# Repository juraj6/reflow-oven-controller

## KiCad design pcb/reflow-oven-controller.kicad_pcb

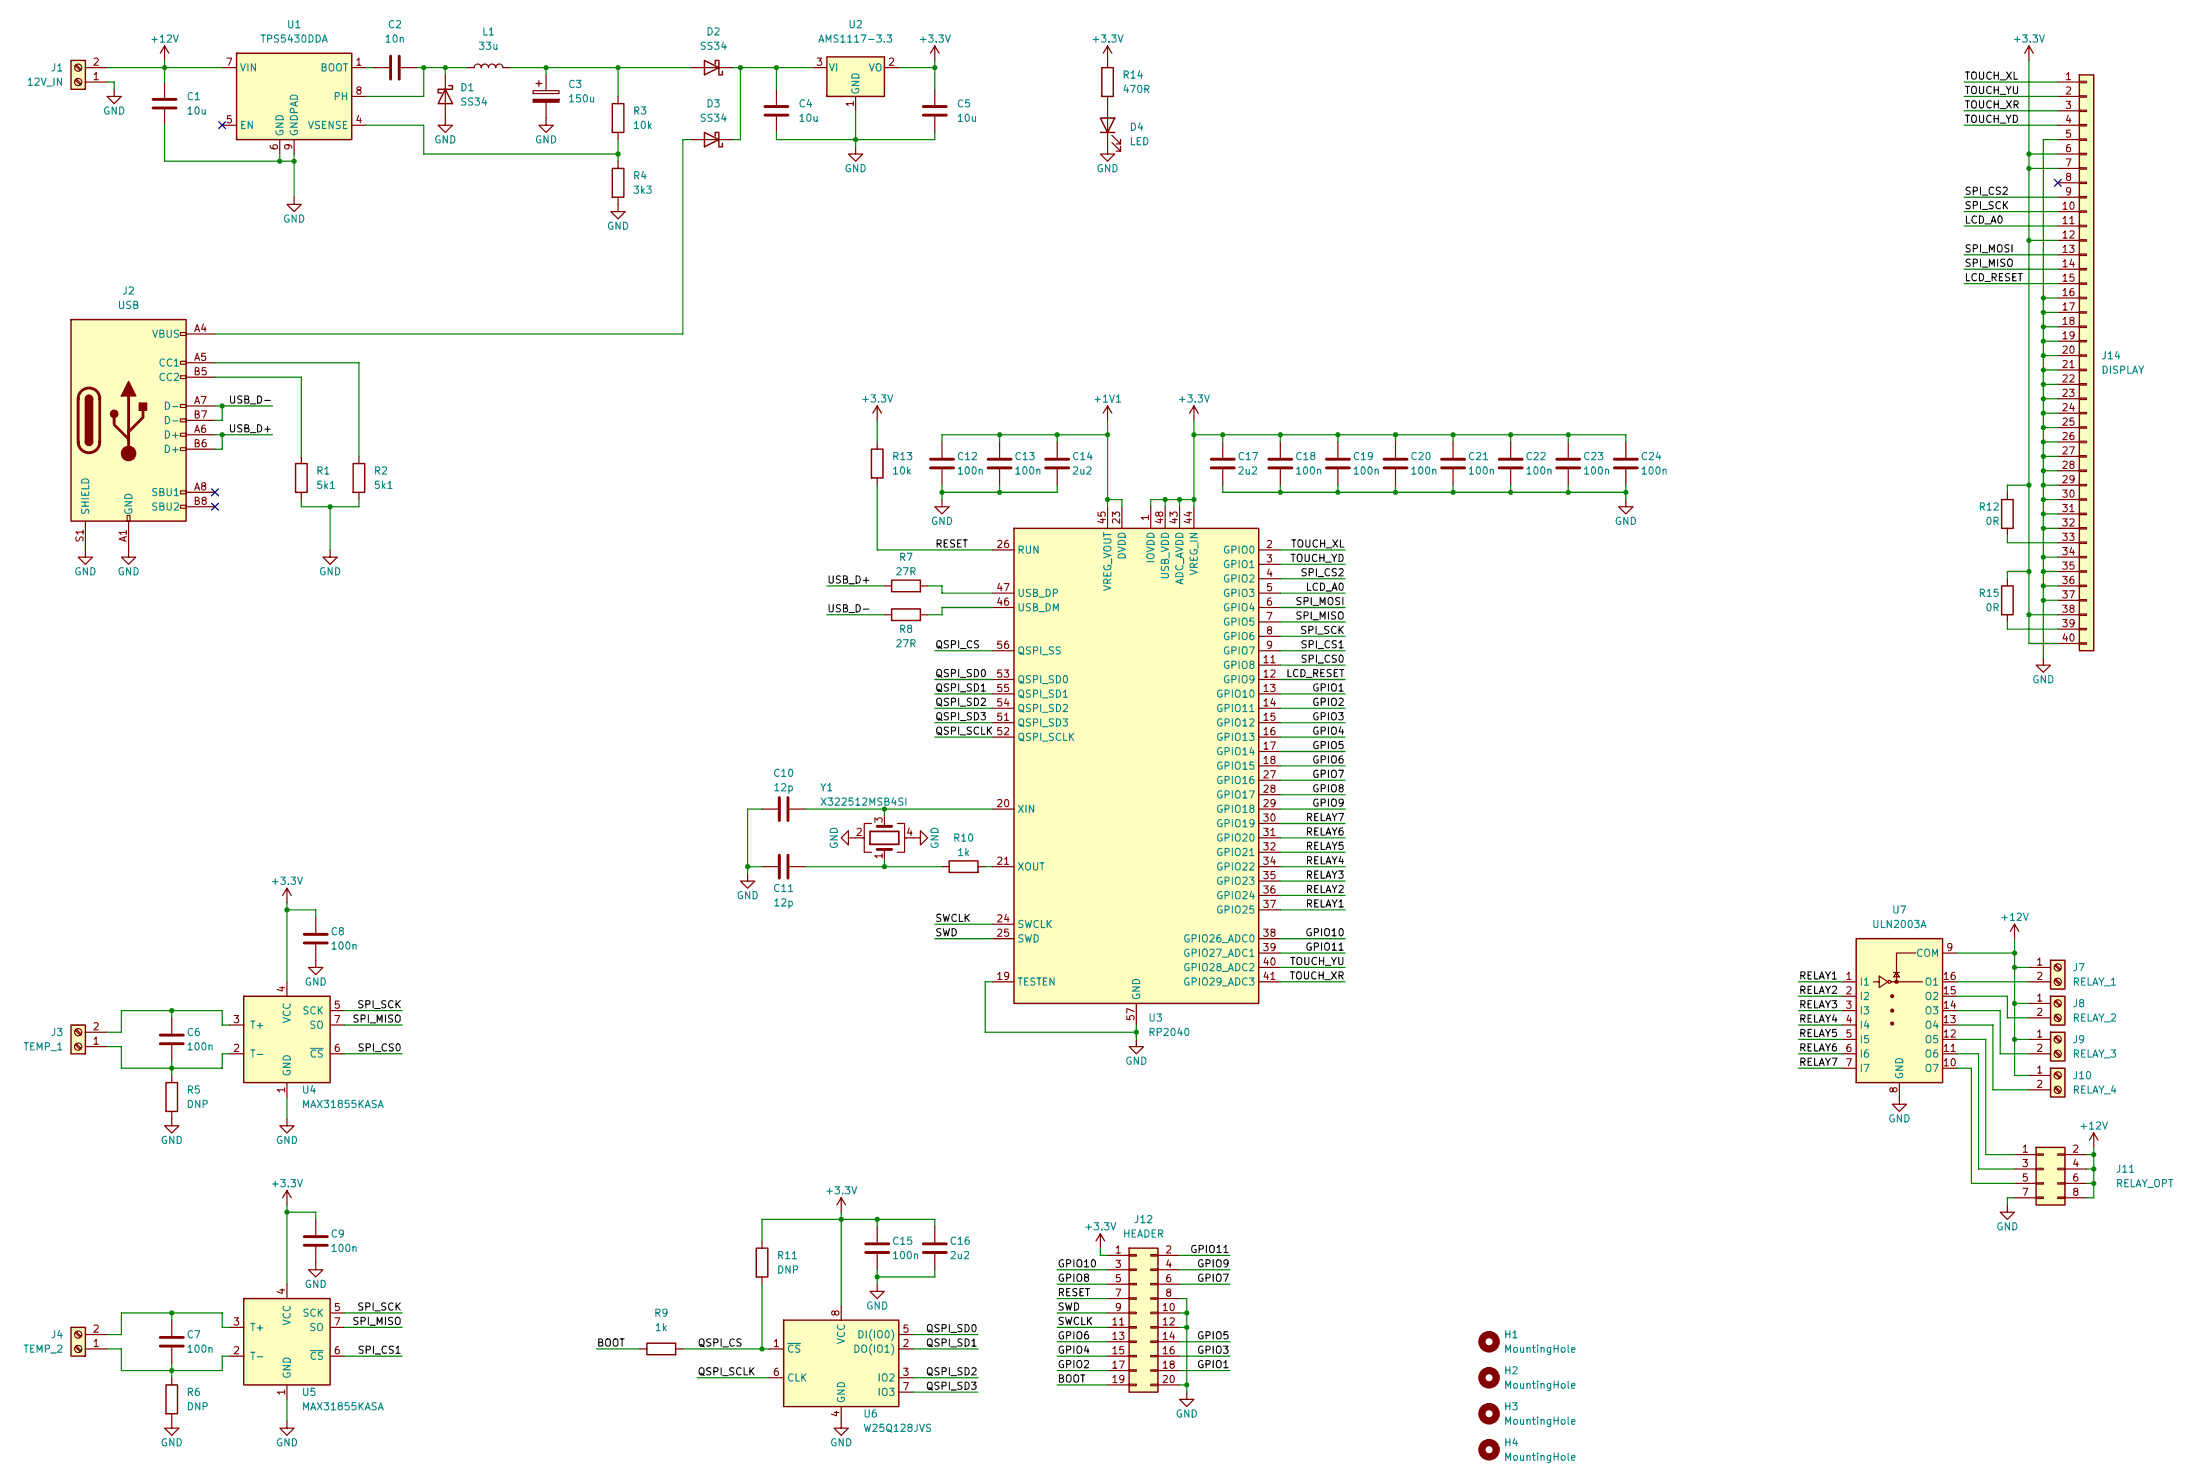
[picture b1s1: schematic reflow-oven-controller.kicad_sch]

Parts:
C1, C4, C5: 10u; C_0805_2012Metric; Tolerance 10%; Voltage 25V; LCSC C15850
C2: 10n; C_0402_1005Metric; Tolerance 10%; Voltage 50V; LCSC C15195
C3: 150u; CP_EIA-7343-15_Kemet-W; Tolerance 20%; Voltage 10V; LCSC C347559
C6, C7, C8, C9, C12, C13, C15, C18, C19, C20, C21, C22, C23, C24: 100n; C_0402_1005Metric; Tolerance 10%; Voltage 16V; LCSC C1525
C10, C11: 12p; C_0402_1005Metric; Tolerance 5%; Voltage 50V; LCSC C1547
C14, C16, C17: 2u2; C_0402_1005Metric; Tolerance 20%; Voltage 6.3V; LCSC C12530
D1, D2, D3: SS34; D_SMA; Voltage 40V; LCSC C8678
D4: LED; LED_0603_1608Metric; LCSC C72043
H1, H2, H3, H4: MountingHole; MountingHole_3.2mm_M3
J1: 12V_IN; TerminalBlock_MetzConnect_Type059_RT06302HBWC_1x02_P3.50mm_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
J2: USB; GCT_USB4145-03-0070-C_REVA2
J3: TEMP_1; TerminalBlock_MetzConnect_Type059_RT06302HBWC_1x02_P3.50mm_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
J4: TEMP_2; TerminalBlock_MetzConnect_Type059_RT06302HBWC_1x02_P3.50mm_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
J7: RELAY_1; TerminalBlock_MetzConnect_Type059_RT06302HBWC_1x02_P3.50mm_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
J8: RELAY_2; TerminalBlock_MetzConnect_Type059_RT06302HBWC_1x02_P3.50mm_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
J9: RELAY_3; TerminalBlock_MetzConnect_Type059_RT06302HBWC_1x02_P3.50mm_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
J10: RELAY_4; TerminalBlock_MetzConnect_Type059_RT06302HBWC_1x02_P3.50mm_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
J11: RELAY_OPT; PinHeader_2x04_P2.54mm_Vertical_SMD
J12: HEADER; PinHeader_2x10_P2.54mm_Vertical_SMD
J14: DISPLAY; Hirose_FH12-40S-0.5SH_1x40-1MP_P0.50mm_Horizontal; LCSC C202114
L1: 33u; L_Taiyo-Yuden_NR-50xx; Tolerance 20%; LCSC C86618
R1, R2: 5k1; R_0402_1005Metric; Tolerance 1%; LCSC C25905
R3, R13: 10k; R_0402_1005Metric; Tolerance 1%; LCSC C25744
R4: 3k3; R_0402_1005Metric; Tolerance 1%; LCSC C25890
R5, R6, R11: DNP; R_0603_1608Metric
R7, R8: 27R; R_0603_1608Metric; Tolerance 1%; LCSC C25190
R9, R10: 1k; R_0402_1005Metric; Tolerance 1%; LCSC C11702
R12, R15: 0R; R_0603_1608Metric; LCSC C21189
R14: 470R; R_0402_1005Metric; Tolerance 1%; LCSC C25117
U1: TPS5430DDA; TI_SO-PowerPAD-8_ThermalVias; LCSC C9864
U2: AMS1117-3.3; SOT-223-3_TabPin2; LCSC C6186
U3: RP2040; QFN-56-1EP_7x7mm_P0.4mm_EP3.2x3.2mm; LCSC C2040
U4, U5: MAX31855KASA; SOIC-8_3.9x4.9mm_P1.27mm; LCSC C52028
U6: W25Q128JVS; SOIC-8_5.23x5.23mm_P1.27mm; LCSC C97521
U7: ULN2003A; SOIC-16_3.9x9.9mm_P1.27mm; LCSC C7512
Y1: X322512MSB4SI; Crystal_SMD_SeikoEpson_TSX3225-4Pin_3.2x2.5mm; LCSC C9002

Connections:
+1V1: C12.1, C13.1, C14.1, U3.23 (DVDD), U3.45 (VREG_VOUT), U3.50 (DVDD)
+3.3V: C5.1, C8.1, C9.1, C15.1, C16.1, C17.1, C18.1, C19.1, C20.1, C21.1, C22.1, C23.1, C24.1, J12.1, J14.6, J14.7, J14.12, J14.38, J14.40, R11.1, R12.1, R13.1, R14.1, R15.1, U2.2 (VO), U3.1 (IOVDD), U3.10 (IOVDD), U3.22 (IOVDD), U3.33 (IOVDD), U3.42 (IOVDD), U3.43 (ADC_AVDD), U3.44 (VREG_IN), U3.48 (USB_VDD), U3.49 (IOVDD), U4.4 (VCC), U5.4 (VCC), U6.8 (VCC)
+12V: C1.1, J1.2, J7.1, J8.1, J9.1, J10.1, J11.2, J11.4, J11.6, J11.8, U1.7 (VIN), U7.9 (COM)
/BOOT: J12.19, R9.1
/GPIO1: J12.18, U3.13 (GPIO10)
/GPIO2: J12.17, U3.14 (GPIO11)
/GPIO3: J12.16, U3.15 (GPIO12)
/GPIO4: J12.15, U3.16 (GPIO13)
/GPIO5: J12.14, U3.17 (GPIO14)
/GPIO6: J12.13, U3.18 (GPIO15)
/GPIO7: J12.6, U3.27 (GPIO16)
/GPIO8: J12.5, U3.28 (GPIO17)
/GPIO9: J12.4, U3.29 (GPIO18)
/GPIO10: J12.3, U3.38 (GPIO26_ADC0)
/GPIO11: J12.2, U3.39 (GPIO27_ADC1)
/LCD_A0: J14.11, U3.5 (GPIO3)
/LCD_RESET: J14.15, U3.12 (GPIO9)
/QSPI_CS: R9.2, R11.2, U3.56 (QSPI_SS), U6.1 (~CS)
/QSPI_SCLK: U3.52 (QSPI_SCLK), U6.6 (CLK)
/QSPI_SD0: U3.53 (QSPI_SD0), U6.5 (DI(IO0))
/QSPI_SD1: U3.55 (QSPI_SD1), U6.2 (DO(IO1))
/QSPI_SD2: U3.54 (QSPI_SD2), U6.3 (IO2)
/QSPI_SD3: U3.51 (QSPI_SD3), U6.7 (IO3)
/RELAY1: U3.37 (GPIO25), U7.1 (I1)
/RELAY2: U3.36 (GPIO24), U7.2 (I2)
/RELAY3: U3.35 (GPIO23), U7.3 (I3)
/RELAY4: U3.34 (GPIO22), U7.4 (I4)
/RELAY5: U3.32 (GPIO21), U7.5 (I5)
/RELAY6: U3.31 (GPIO20), U7.6 (I6)
/RELAY7: U3.30 (GPIO19), U7.7 (I7)
/RESET: J12.7, R13.2, U3.26 (RUN)
/SPI_CS0: U3.11 (GPIO8), U4.6 (~CS)
/SPI_CS1: U3.9 (GPIO7), U5.6 (~CS)
/SPI_CS2: J14.9, U3.4 (GPIO2)
/SPI_MISO: J14.14, U3.7 (GPIO5), U4.7 (SO), U5.7 (SO)
/SPI_MOSI: J14.13, U3.6 (GPIO4)
/SPI_SCK: J14.10, U3.8 (GPIO6), U4.5 (SCK), U5.5 (SCK)
/SWCLK: J12.11, U3.24 (SWCLK)
/SWD: J12.9, U3.25 (SWD)
/TOUCH_XL: J14.1, U3.2 (GPIO0)
/TOUCH_XR: J14.3, U3.41 (GPIO29_ADC3)
/TOUCH_YD: J14.4, U3.3 (GPIO1)
/TOUCH_YU: J14.2, U3.40 (GPIO28_ADC2)
/USB_D+: J2.A6 (D+), J2.B6 (D+), R7.1
/USB_D-: J2.A7 (D-), J2.B7 (D-), R8.1
GND: C1.2, C3.2, C4.2, C5.2, C8.2, C9.2, C10.1, C11.1, C12.2, C13.2, C14.2, C15.2, C16.2, C17.2, C18.2, C19.2, C20.2, C21.2, C22.2, C23.2, C24.2, D1.2 (A), D4.1 (K), J1.1, J2.A1 (GND), J2.A12 (GND), J2.B1 (GND), J2.B12 (GND), J2.S1 (SHIELD), J11.7, J12.8, J12.10, J12.12, J12.20, J14.5, J14.16, J14.17, J14.18, J14.19, J14.20, J14.21, J14.22, J14.23, J14.24, J14.25, J14.26, J14.27, J14.28, J14.29, J14.30, J14.31, J14.32, J14.34, J14.35, J14.36, J14.37, R1.2, R2.2, R4.2, R5.2, R6.2, U1.6 (GND), U1.9 (GNDPAD), U2.1 (GND), U3.19 (TESTEN), U3.57 (GND), U4.1 (GND), U5.1 (GND), U6.4 (GND), U7.8 (GND), Y1.2, Y1.4
unnamed: C2.1, U1.1 (BOOT)
unnamed: C2.2, D1.1 (K), L1.1, U1.8 (PH)
unnamed: C3.1, D2.2 (A), L1.2, R3.1
unnamed: C4.1, D2.1 (K), D3.1 (K), U2.3 (VI)
unnamed: C6.1, J3.2, U4.3 (T+)
unnamed: C6.2, J3.1, R5.1, U4.2 (T-)
unnamed: C7.1, J4.2, U5.3 (T+)
unnamed: C7.2, J4.1, R6.1, U5.2 (T-)
unnamed: C10.2, U3.20 (XIN), Y1.3
unnamed: C11.2, R10.1, Y1.1
unnamed: D3.2 (A), J2.A4 (VBUS), J2.A9 (VBUS), J2.B4 (VBUS), J2.B9 (VBUS)
unnamed: D4.2 (A), R14.2
unnamed: J2.A5 (CC1), R2.1
unnamed: J2.B5 (CC2), R1.1
unnamed: J7.2, U7.16 (O1)
unnamed: J8.2, U7.15 (O2)
unnamed: J9.2, U7.14 (O3)
unnamed: J10.2, U7.13 (O4)
unnamed: J11.1, U7.12 (O5)
unnamed: J11.3, U7.11 (O6)
unnamed: J11.5, U7.10 (O7)
unnamed: J14.33, R12.2
unnamed: J14.39, R15.2
unnamed: R3.2, R4.1, U1.4 (VSENSE)
unnamed: R7.2, U3.47 (USB_DP)
unnamed: R8.2, U3.46 (USB_DM)
unnamed: R10.2, U3.21 (XOUT)

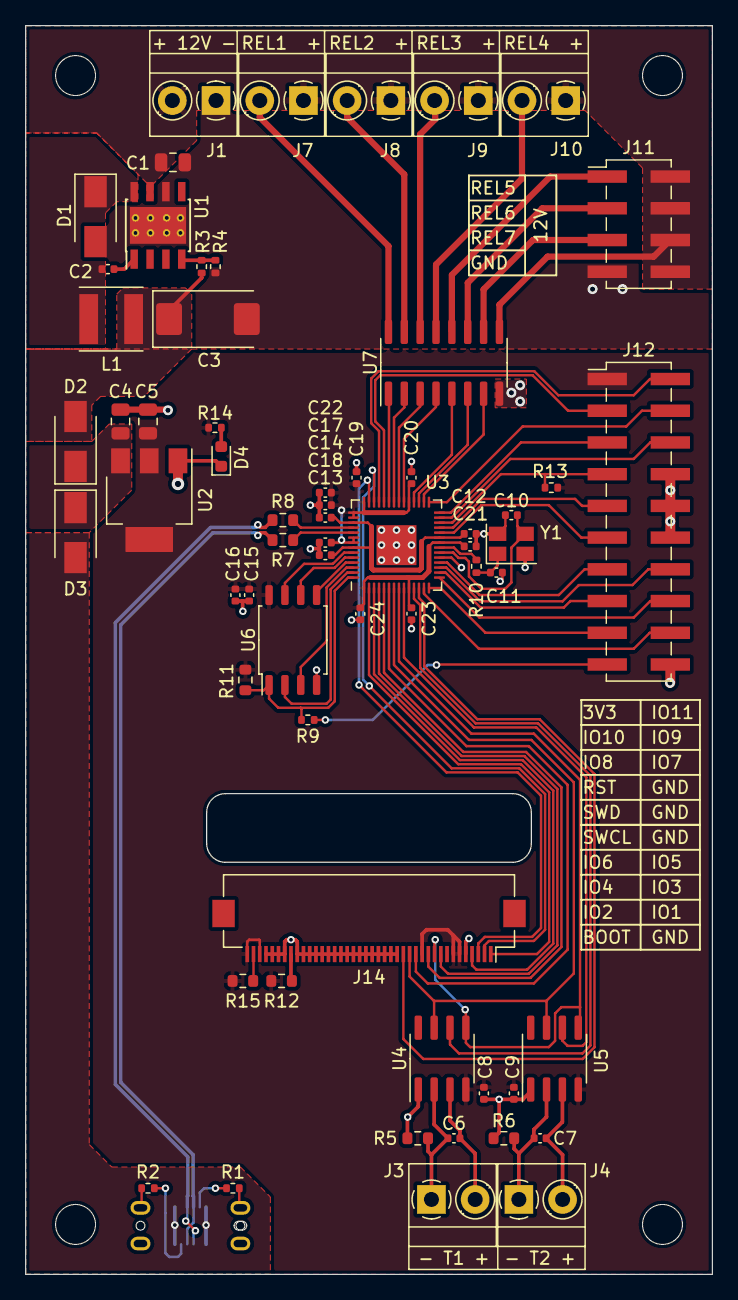
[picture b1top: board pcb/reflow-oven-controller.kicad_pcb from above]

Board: 2 copper layers, 55.0 x 100.0 mm, 67 parts (1 on the bottom side), 73 nets.

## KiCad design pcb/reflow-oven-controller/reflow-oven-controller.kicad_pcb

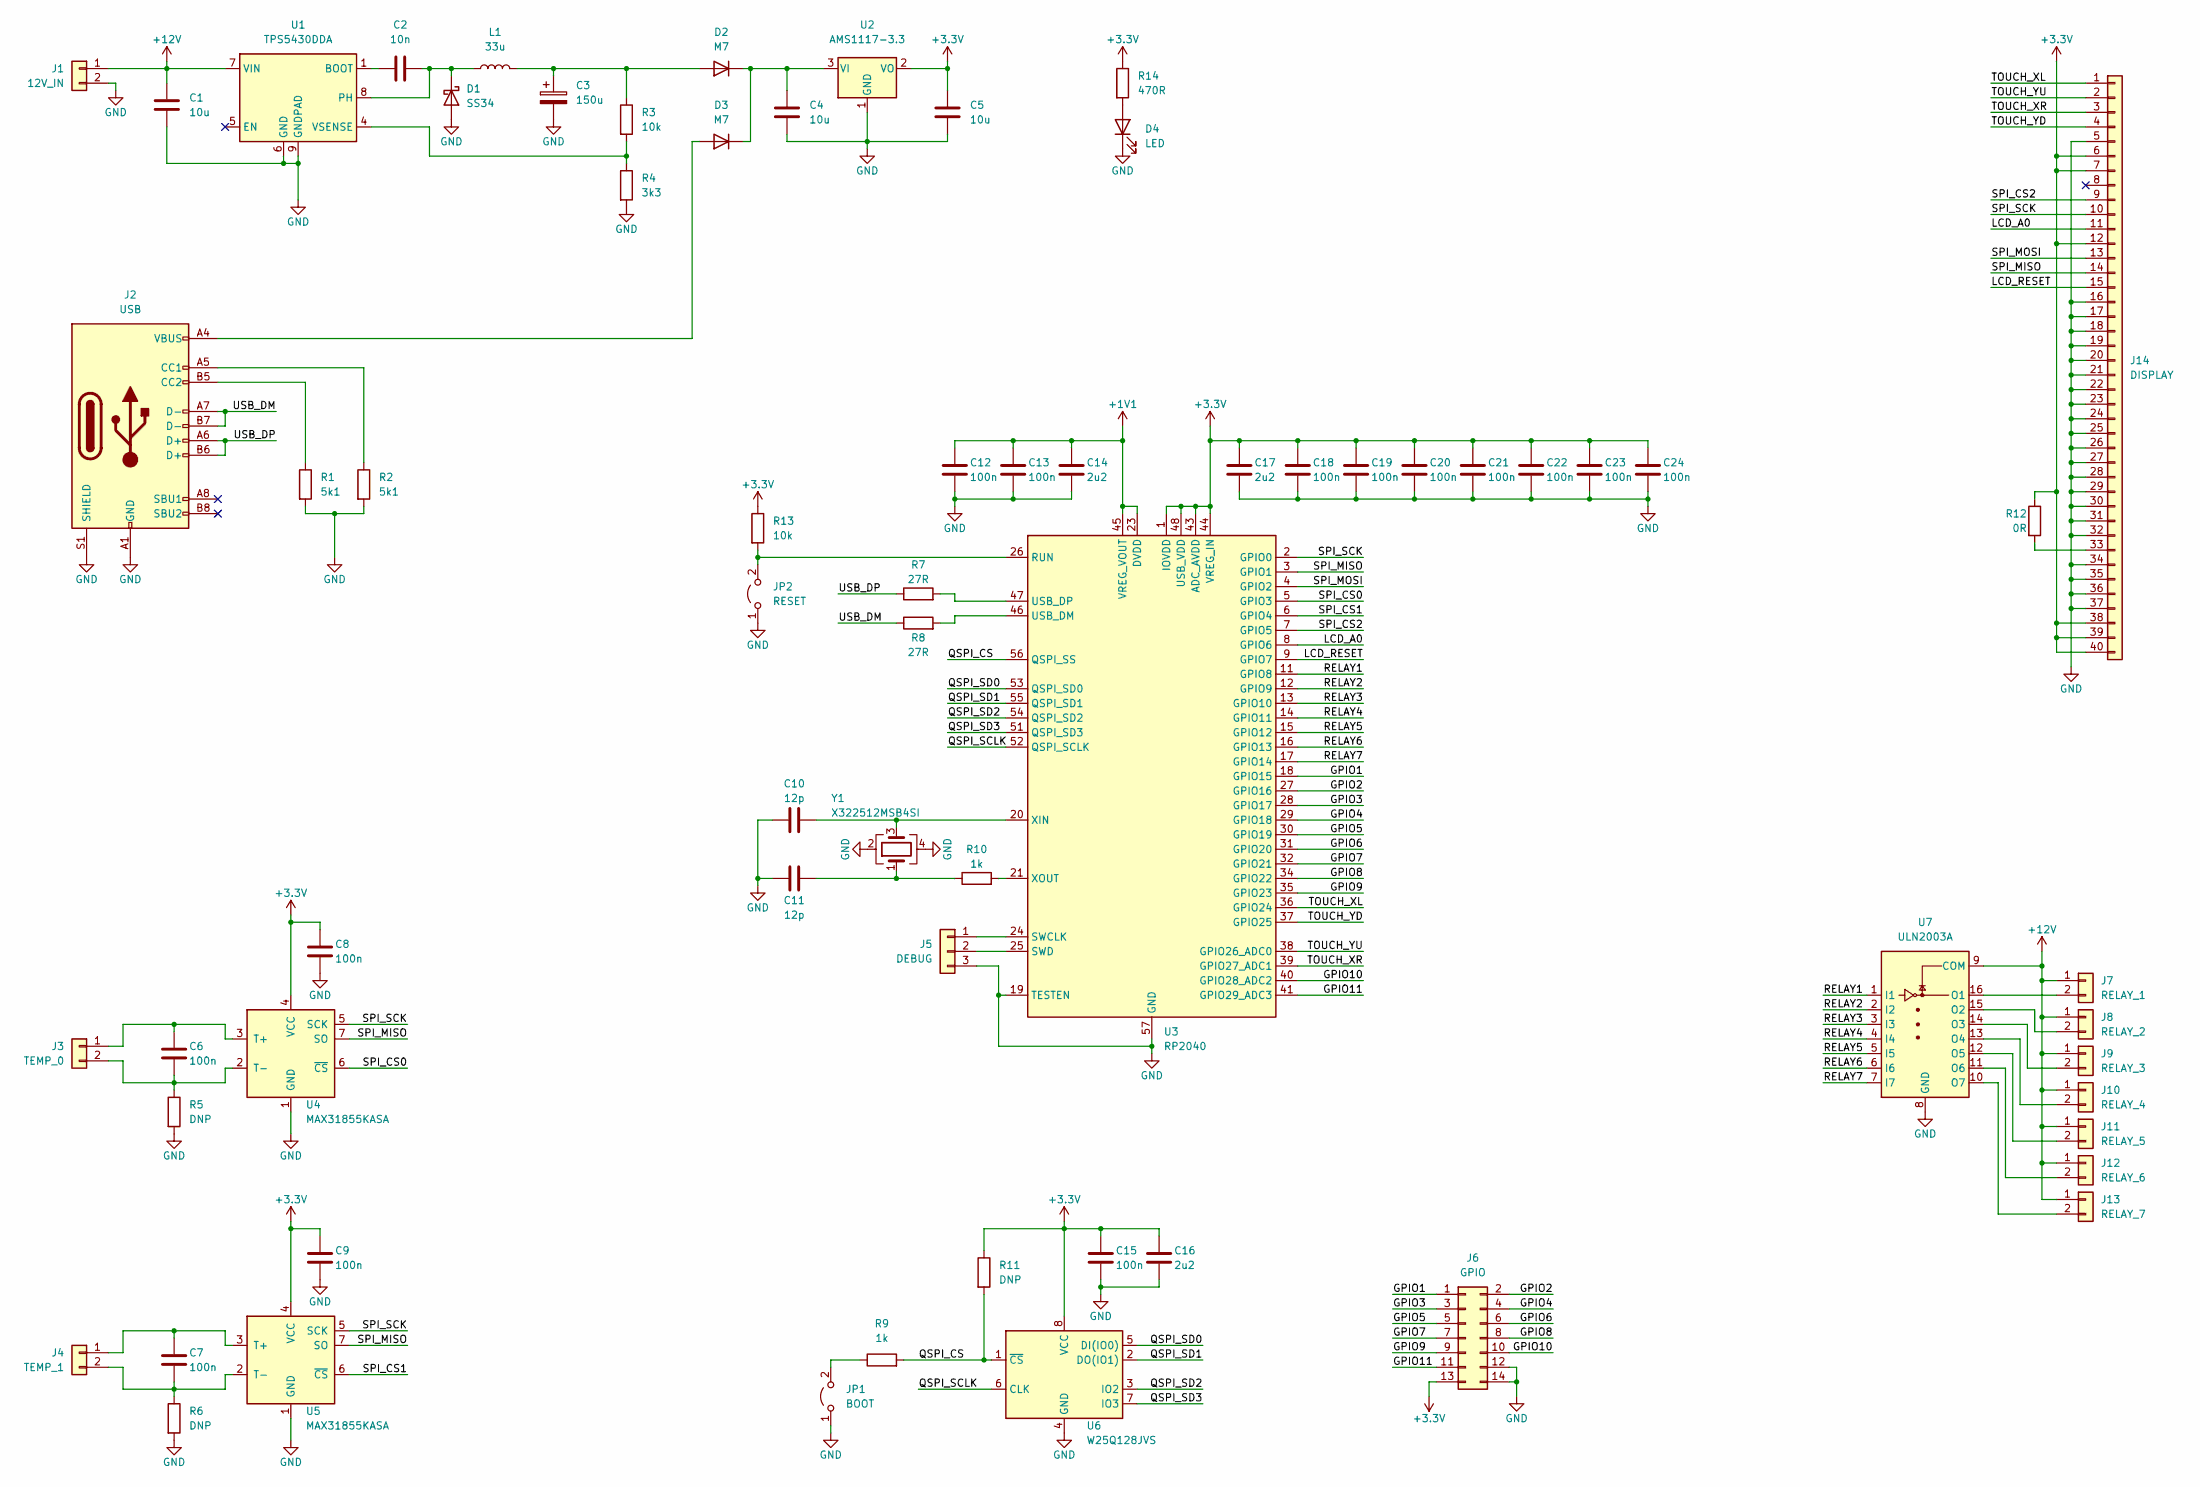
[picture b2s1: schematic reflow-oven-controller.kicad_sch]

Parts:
C1, C4, C5: 10u; C_0805_2012Metric; Tolerance 10%; Voltage 25V; LCSC C15850
C2: 10n; C_0402_1005Metric; Tolerance 10%; Voltage 50V; LCSC C15195
C3: 150u; CP_EIA-7343-15_Kemet-W; Tolerance 20%; Voltage 10V; LCSC C347559
C6, C7, C8, C9, C12, C13, C15, C18, C19, C20, C21, C22, C23, C24: 100n; C_0402_1005Metric; Tolerance 10%; Voltage 16V; LCSC C1525
C10, C11: 12p; C_0402_1005Metric; Tolerance 5%; Voltage 50V; LCSC C1547
C14, C16, C17: 2u2; C_0402_1005Metric; Tolerance 20%; Voltage 6.3V; LCSC C12530
D1: SS34; D_SMA; Voltage 40V; LCSC C8678
D2, D3: M7; D_SMA; LCSC C95872
D4: LED; LED_0603_1608Metric; LCSC C72043
J1: 12V_IN; TerminalBlock_MetzConnect_Type059_RT06302HBWC_1x02_P3.50mm_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
J2: USB; USB_C_Receptacle_GCT_USB4115-03-C; LCSC C381139
J3: TEMP_0; TerminalBlock_MetzConnect_Type059_RT06302HBWC_1x02_P3.50mm_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
J4: TEMP_1; TerminalBlock_MetzConnect_Type059_RT06302HBWC_1x02_P3.50mm_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
J5: DEBUG; PinHeader_1x03_P2.54mm_Vertical
J6: GPIO; PinHeader_2x07_P2.54mm_Vertical
J7: RELAY_1; TerminalBlock_MetzConnect_Type059_RT06302HBWC_1x02_P3.50mm_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
J8: RELAY_2; TerminalBlock_MetzConnect_Type059_RT06302HBWC_1x02_P3.50mm_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
J9: RELAY_3; TerminalBlock_MetzConnect_Type059_RT06302HBWC_1x02_P3.50mm_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
J10: RELAY_4; TerminalBlock_MetzConnect_Type059_RT06302HBWC_1x02_P3.50mm_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
J11: RELAY_5; TerminalBlock_MetzConnect_Type059_RT06302HBWC_1x02_P3.50mm_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
J12: RELAY_6; TerminalBlock_MetzConnect_Type059_RT06302HBWC_1x02_P3.50mm_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
J13: RELAY_7; TerminalBlock_MetzConnect_Type059_RT06302HBWC_1x02_P3.50mm_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
J14: DISPLAY; Hirose_FH12-40S-0.5SH_1x40-1MP_P0.50mm_Horizontal; LCSC C202114
JP1: BOOT; PinHeader_1x02_P2.54mm_Vertical
JP2: RESET; PinHeader_1x02_P2.54mm_Vertical
L1: 33u; L_Taiyo-Yuden_NR-50xx; Tolerance 20%; LCSC C86618
R1, R2: 5k1; R_0402_1005Metric; Tolerance 1%; LCSC C25905
R3, R13: 10k; R_0402_1005Metric; Tolerance 1%; LCSC C25744
R4: 3k3; R_0402_1005Metric; Tolerance 1%; LCSC C25890
R5, R6, R11: DNP; R_0603_1608Metric
R7, R8: 27R; R_0603_1608Metric; Tolerance 1%; LCSC C25190
R9, R10: 1k; R_0402_1005Metric; Tolerance 1%; LCSC C11702
R12: 0R; R_0603_1608Metric; LCSC C21189
R14: 470R; R_0402_1005Metric; Tolerance 1%; LCSC C25117
U1: TPS5430DDA; TI_SO-PowerPAD-8_ThermalVias; LCSC C9864
U2: AMS1117-3.3; SOT-223-3_TabPin2; LCSC C6186
U3: RP2040; QFN-56-1EP_7x7mm_P0.4mm_EP3.2x3.2mm; LCSC C2040
U4, U5: MAX31855KASA; SOIC-8_3.9x4.9mm_P1.27mm; LCSC C52028
U6: W25Q128JVS; SOIC-8_5.23x5.23mm_P1.27mm; LCSC C97521
U7: ULN2003A; SOIC-16_3.9x9.9mm_P1.27mm; LCSC C7512
Y1: X322512MSB4SI; Crystal_SMD_SeikoEpson_TSX3225-4Pin_3.2x2.5mm; LCSC C9002

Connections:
+1V1: C12.1, C13.1, C14.1, U3.23 (DVDD), U3.45 (VREG_VOUT), U3.50 (DVDD)
+12V: C1.1, J1.1, J7.1, J8.1, J9.1, J10.1, J11.1, J12.1, J13.1, U1.7 (VIN), U7.9 (COM)
/GPIO1: J6.1, U3.18 (GPIO15)
/GPIO2: J6.2, U3.27 (GPIO16)
/GPIO3: J6.3, U3.28 (GPIO17)
/GPIO4: J6.4, U3.29 (GPIO18)
/GPIO5: J6.5, U3.30 (GPIO19)
/GPIO6: J6.6, U3.31 (GPIO20)
/GPIO7: J6.7, U3.32 (GPIO21)
/GPIO8: J6.8, U3.34 (GPIO22)
/GPIO9: J6.9, U3.35 (GPIO23)
/GPIO10: J6.10, U3.40 (GPIO28_ADC2)
/GPIO11: J6.11, U3.41 (GPIO29_ADC3)
/LCD_A0: J14.11, U3.8 (GPIO6)
/LCD_RESET: J14.15, U3.9 (GPIO7)
/QSPI_CS: R9.2, R11.2, U3.56 (QSPI_SS), U6.1 (~CS)
/QSPI_SCLK: U3.52 (QSPI_SCLK), U6.6 (CLK)
/QSPI_SD0: U3.53 (QSPI_SD0), U6.5 (DI(IO0))
/QSPI_SD1: U3.55 (QSPI_SD1), U6.2 (DO(IO1))
/QSPI_SD2: U3.54 (QSPI_SD2), U6.3 (IO2)
/QSPI_SD3: U3.51 (QSPI_SD3), U6.7 (IO3)
/RELAY1: U3.11 (GPIO8), U7.1 (I1)
/RELAY2: U3.12 (GPIO9), U7.2 (I2)
/RELAY3: U3.13 (GPIO10), U7.3 (I3)
/RELAY4: U3.14 (GPIO11), U7.4 (I4)
/RELAY5: U3.15 (GPIO12), U7.5 (I5)
/RELAY6: U3.16 (GPIO13), U7.6 (I6)
/RELAY7: U3.17 (GPIO14), U7.7 (I7)
/SPI_CS0: U3.5 (GPIO3), U4.6 (~CS)
/SPI_CS1: U3.6 (GPIO4), U5.6 (~CS)
/SPI_CS2: J14.9, U3.7 (GPIO5)
/SPI_MISO: J14.14, U3.3 (GPIO1), U4.7 (SO), U5.7 (SO)
/SPI_MOSI: J14.13, U3.4 (GPIO2)
/SPI_SCK: J14.10, U3.2 (GPIO0), U4.5 (SCK), U5.5 (SCK)
/TOUCH_XL: J14.1, U3.36 (GPIO24)
/TOUCH_XR: J14.3, U3.39 (GPIO27_ADC1)
/TOUCH_YD: J14.4, U3.37 (GPIO25)
/TOUCH_YU: J14.2, U3.38 (GPIO26_ADC0)
/USB_DM: J2.A7 (D-), J2.B7 (D-), R8.1
/USB_DP: J2.A6 (D+), J2.B6 (D+), R7.1
unnamed: C2.1, U1.1 (BOOT)
unnamed: C2.2, D1.1 (K), L1.1, U1.8 (PH)
unnamed: C3.1, D2.2 (A), L1.2, R3.1
unnamed: C4.1, D2.1 (K), D3.1 (K), U2.3 (VI)
unnamed: C6.1, J3.1, U4.3 (T+)
unnamed: C6.2, J3.2, R5.1, U4.2 (T-)
unnamed: C7.1, J4.1, U5.3 (T+)
unnamed: C7.2, J4.2, R6.1, U5.2 (T-)
unnamed: C10.2, U3.20 (XIN), Y1.3
unnamed: C11.2, R10.1, Y1.1
unnamed: J2.A5 (CC1), R2.1
unnamed: J2.B5 (CC2), R1.1
unnamed: J5.1, U3.24 (SWCLK)
unnamed: J5.2, U3.25 (SWD)
unnamed: J7.2, U7.16 (O1)
unnamed: J8.2, U7.15 (O2)
unnamed: J9.2, U7.14 (O3)
unnamed: J10.2, U7.13 (O4)
unnamed: J11.2, U7.12 (O5)
unnamed: J12.2, U7.11 (O6)
unnamed: J13.2, U7.10 (O7)
unnamed: J14.33, R12.2
unnamed: JP1.2 (B), R9.1
unnamed 63: D4.2 (A), R14.2; also elsewhere on the board
unnamed: R3.2, R4.1, U1.4 (VSENSE)
unnamed: R7.2, U3.47 (USB_DP)
unnamed: R8.2, U3.46 (USB_DM)
unnamed: R10.2, U3.21 (XOUT)

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
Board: 2 copper layers, 68 parts (0 on the bottom side), 72 nets, no tracks yet.

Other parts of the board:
Q1: AO3400A; SOT-23
R13#2: 10k; R_0402_1005Metric

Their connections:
unnamed 63: Q1.1 (G); also elsewhere on the board

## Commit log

2023-05-03 Create schematic
2023-05-07 Finish PCB
2023-05-07 Remove unnecessary parent dir
2023-05-08 Add missing 3D models
